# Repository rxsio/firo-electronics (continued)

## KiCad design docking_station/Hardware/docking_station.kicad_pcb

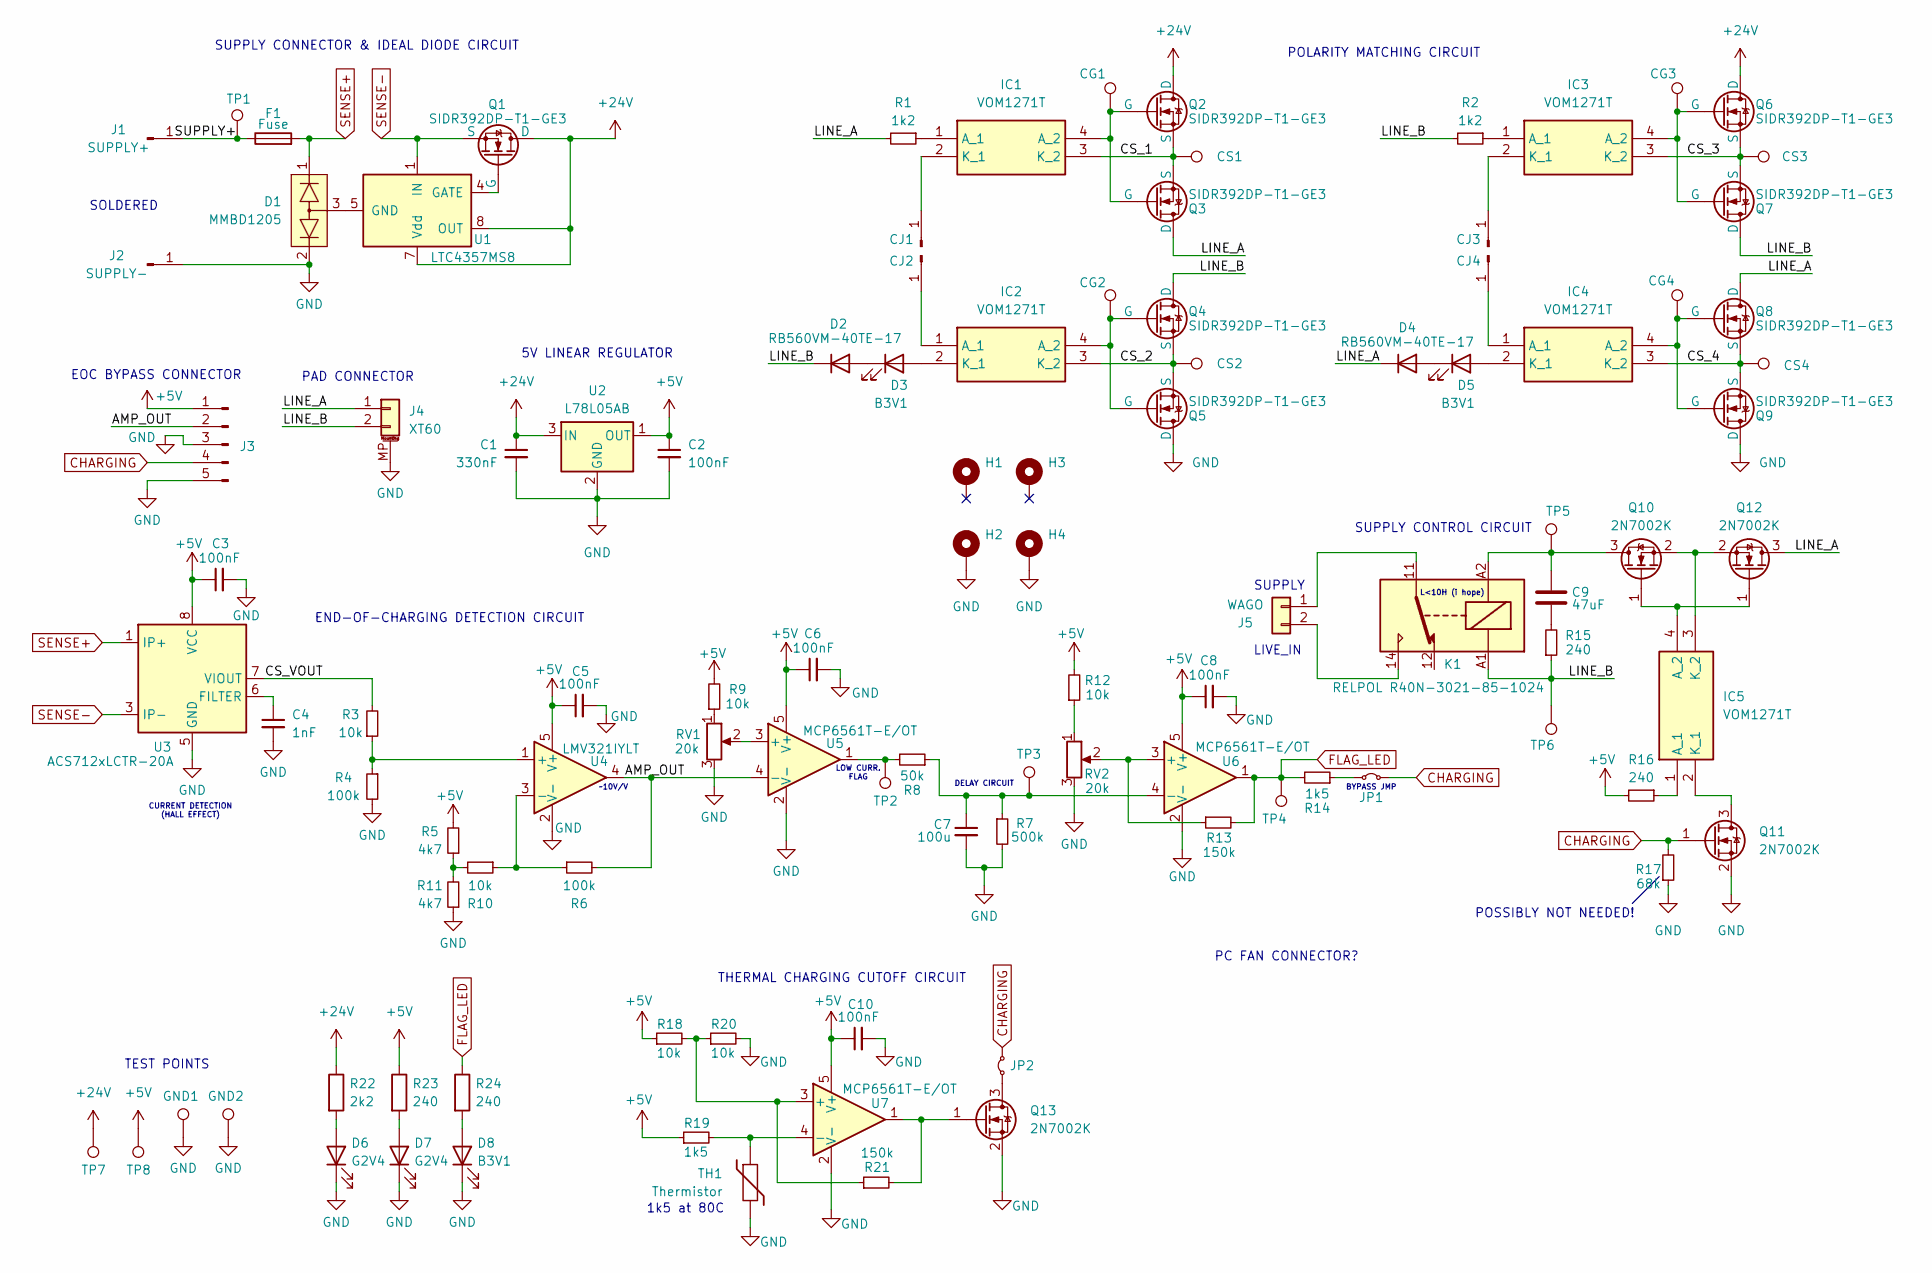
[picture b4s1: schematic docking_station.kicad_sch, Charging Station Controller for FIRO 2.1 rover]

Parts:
C1: 330nF; C_0805_2012Metric
C2, C3, C5, C6, C8, C10: 100nF; C_0805_2012Metric
C4: 1nF; C_0805_2012Metric
C7: 100u; C_1206_3216Metric
C9: 47uF; C_2220_5750Metric
CG1, CG2, CG3, CG4: TestPoint; TestPoint_Pad_D2.0mm
CJ1, CJ2, CJ3, CJ4: 20AWG SMD
CS1, CS2, CS3, CS4: TestPoint; TestPoint_Pad_D2.0mm
D1: MMBD1205; SOT-23
D2, D4: RB560VM-40TE-17; D_SOD-323F
D3, D5, D8: B3V1; LED_0805_2012Metric
D6, D7: G2V4; LED_0805_2012Metric
F1: Fuse; firo_fuse
GND1, GND2: TestPoint; TestPoint_Bridge_Pitch3.81mm_Drill1.3mm
H1, H2, H3, H4: MountingHole_Pad; MountingHole_3.2mm_M3_Pad_Via
IC1, IC2, IC3, IC4, IC5: VOM1271T; SOP254P675X240-4N; Manufacturer_Part_Number VOM1271T
J1: SUPPLY+; 14 AWG THT
J2: SUPPLY-; 14 AWG THT
J3: Conn_01x05_Pin; PinHeader_1x05_P2.54mm_Vertical
J4: XT60; AMASS_XT60PW-F-MP
J5: WAGO; WAGO 2601-3102
JP1, JP2: Jumper_2_Small_Bridged; SolderJumper-2_P1.3mm_Bridged2Bar_RoundedPad1.0x1.5mm
K1: RELPOL R40N-3021-85-1024; Relpol R40N
Q1, Q2, Q3, Q4, Q5, Q6, Q7, Q8, Q9: SIDR392DP-T1-GE3; PowerPAK_SO-8DC for VISHAY SIDR392DP-T1-GE3
Q10, Q11, Q12, Q13: 2N7002K; SOT-23
R1, R2: 1k2; R_1206_3216Metric
R3, R9, R10, R12, R18, R20: 10k; R_0402_1005Metric
R4, R6: 100k; R_0402_1005Metric
R5, R11: 4k7; R_0402_1005Metric
R7: 500k; R_0402_1005Metric
R8: 50k; R_0402_1005Metric
R13, R21: 150k; R_0402_1005Metric
R14, R19: 1k5; R_0402_1005Metric
R15, R16, R23, R24: 240; R_0805_2012Metric
R17: 68k; R_0402_1005Metric
R22: 2k2; R_1206_3216Metric
RV1, RV2: 20k; BOURNS_3313J-1_SMD
TH1: Thermistor; R_Axial_DIN0204_L3.6mm_D1.6mm_P2.54mm_Vertical
TP1, TP2, TP3, TP4, TP5, TP6, TP7, TP8: TestPoint; TestPoint_Pad_D2.0mm
U1: LTC4357MS8; MSOP-8_3x3mm_P0.65mm
U2: L78L05AB; SOT-89-3
U3: ACS712xLCTR-20A; SOIC-8_3.9x4.9mm_P1.27mm
U4: LMV321IYLT; SOT-23-5
U5, U6, U7: MCP6561T-E/OT; SOT-23-5

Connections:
+5V: C2.1, C3.1, C5.1, C6.1, C8.1, C10.1, J3.1, R5.2, R9.2, R12.2, R16.2, R18.1, R19.1, R23.1, TP8.1, U2.1 (OUT), U3.8 (VCC), U4.5 (V+), U5.5 (V+), U6.5 (V+), U7.5 (V+)
+24V: C1.1, Q1.3 (D), Q2.3 (D), Q6.3 (D), R22.1, TP7.1, U1.7 (Vdd), U1.8 (OUT), U2.3 (IN)
/AMP_OUT: J3.2, R6.2, U4.4, U5.4 (-)
/CS_1: CS1.1, IC1.3 (K_2), Q2.1 (S), Q3.1 (S)
/CS_2: CS2.1, IC2.3 (K_2), Q4.1 (S), Q5.1 (S)
/CS_3: CS3.1, IC3.3 (K_2), Q6.1 (S), Q7.1 (S)
/CS_4: CS4.1, IC4.3 (K_2), Q8.1 (S), Q9.1 (S)
/CS_VOUT: R3.2, U3.7 (VIOUT)
/LINE_A: D4.1 (K), J4.1, Q3.3 (D), Q8.3 (D), Q12.3 (D), R1.2
/LINE_B: D2.1 (K), J4.2, K1.A1, Q4.3 (D), Q7.3 (D), R2.2, R15.1, TP6.1
/SUPPLY+: F1.1, J1.1, TP1.1
CHARGING: J3.4, JP1.2 (B), JP2.2 (B), Q11.1 (G), R17.2
FLAG_LED: R13.2, R14.2, R24.1, TP4.1, U6.1
GND: C1.2, C2.2, C3.2, C4.2, C5.2, C6.2, C7.2, C8.2, C10.2, D1.2, D6.1 (K), D7.1 (K), D8.1 (K), GND1.1, GND2.1, H2.1, H4.1, J2.1, J3.3, J3.5, J4.MP (MountPin), Q5.3 (D), Q9.3 (D), Q11.2 (S), Q13.2 (S), R4.2, R7.2, R11.1, R17.1, R20.2, RV1.3, RV2.3, TH1.2, U2.2 (GND), U3.5 (GND), U4.2 (V-), U5.2 (V-), U6.2 (V-), U7.2 (V-)
unnamed: C9.2, R15.2
unnamed: CJ1.1, IC1.2 (K_1)
unnamed: CJ2.1, IC2.1 (A_1)
unnamed: CJ3.1, IC3.2 (K_1)
unnamed: CJ4.1, IC4.1 (A_1)
unnamed: D2.2 (A), D3.1 (K)
unnamed: D3.2 (A), IC2.2 (K_1)
unnamed: D4.2 (A), D5.1 (K)
unnamed: D5.2 (A), IC4.2 (K_1)
unnamed: D6.2 (A), R22.2
unnamed: D7.2 (A), R23.2
unnamed: D8.2 (A), R24.2
unnamed: IC1.1 (A_1), R1.1
unnamed: CG1.1, IC1.4 (A_2), Q2.2 (G), Q3.2 (G)
unnamed: CG2.1, IC2.4 (A_2), Q4.2 (G), Q5.2 (G)
unnamed: IC3.1 (A_1), R2.1
unnamed: CG3.1, IC3.4 (A_2), Q6.2 (G), Q7.2 (G)
unnamed: CG4.1, IC4.4 (A_2), Q8.2 (G), Q9.2 (G)
unnamed: IC5.1 (A_1), R16.1
unnamed: IC5.4 (A_2), Q10.1 (G), Q12.1 (G)
unnamed: IC5.2 (K_1), Q11.3 (D)
unnamed: IC5.3 (K_2), Q10.2 (S), Q12.2 (S)
unnamed: J5.1, K1.11
unnamed: J5.2, K1.14
unnamed: JP1.1 (A), R14.1
unnamed: JP2.1 (A), Q13.3 (D)
unnamed: Q1.2 (G), U1.4 (GATE)
unnamed: C9.1, K1.A2, Q10.3 (D), TP5.1
unnamed: Q13.1 (G), R21.2, U7.1
unnamed: R8.2, TP2.1, U5.1
unnamed: R9.1, RV1.1
unnamed: R5.1, R10.2, R11.2
unnamed: R12.1, RV2.1
unnamed: D1.3, U1.5 (GND)
unnamed: C4.1, U3.6 (FILTER)
unnamed: R3.1, R4.1, U4.1 (+)
unnamed: R6.1, R10.1, U4.3 (-)
unnamed: RV1.2, U5.3 (+)
unnamed: R13.1, RV2.2, U6.3 (+)
unnamed: C7.1, R7.1, R8.1, TP3.1, U6.4 (-)
unnamed: R18.2, R20.1, R21.1, U7.3 (+)
unnamed: R19.2, TH1.1, U7.4 (-)
SENSE+: D1.1, F1.2, U3.1 (IP+), U3.2 (IP+)
SENSE-: Q1.1 (S), U1.1 (IN), U3.3 (IP-), U3.4 (IP-)

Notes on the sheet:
EOC BYPASS CONNECTOR
PC FAN CONNECTOR?
END-OF-CHARGING DETECTION CIRCUIT
~10V/V
SOLDERED
SUPPLY CONNECTOR & IDEAL DIODE CIRCUIT
5V LINEAR REGULATOR
1k5 at 80C
SUPPLY CONTROL CIRCUIT
CURRENT DETECTION (HALL EFFECT)
LIVE_IN
LOW CURR. FLAG
POSSIBLY NOT NEEDED!
DELAY CIRCUIT
PAD CONNECTOR
POLARITY MATCHING CIRCUIT
BYPASS JMP
TEST POINTS
SUPPLY
THERMAL CHARGING CUTOFF CIRCUIT
L<10H (i hope)

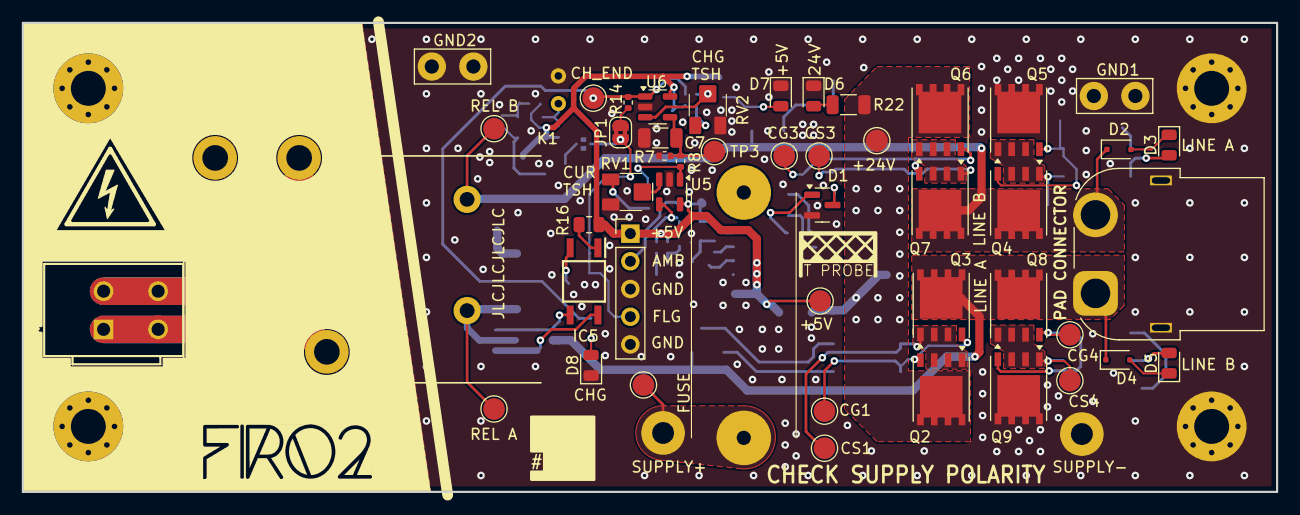
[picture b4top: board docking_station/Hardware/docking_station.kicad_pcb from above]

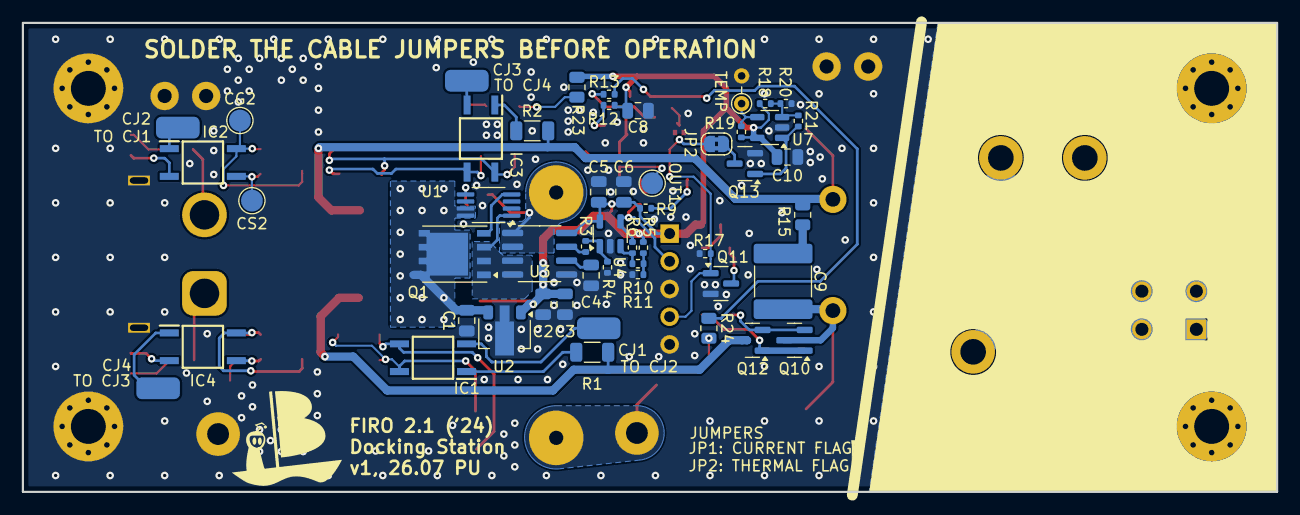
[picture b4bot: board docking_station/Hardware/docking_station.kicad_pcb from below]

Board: 2 copper layers, 115.0 x 43.0 mm, 105 parts (51 on the bottom side), 58 nets.

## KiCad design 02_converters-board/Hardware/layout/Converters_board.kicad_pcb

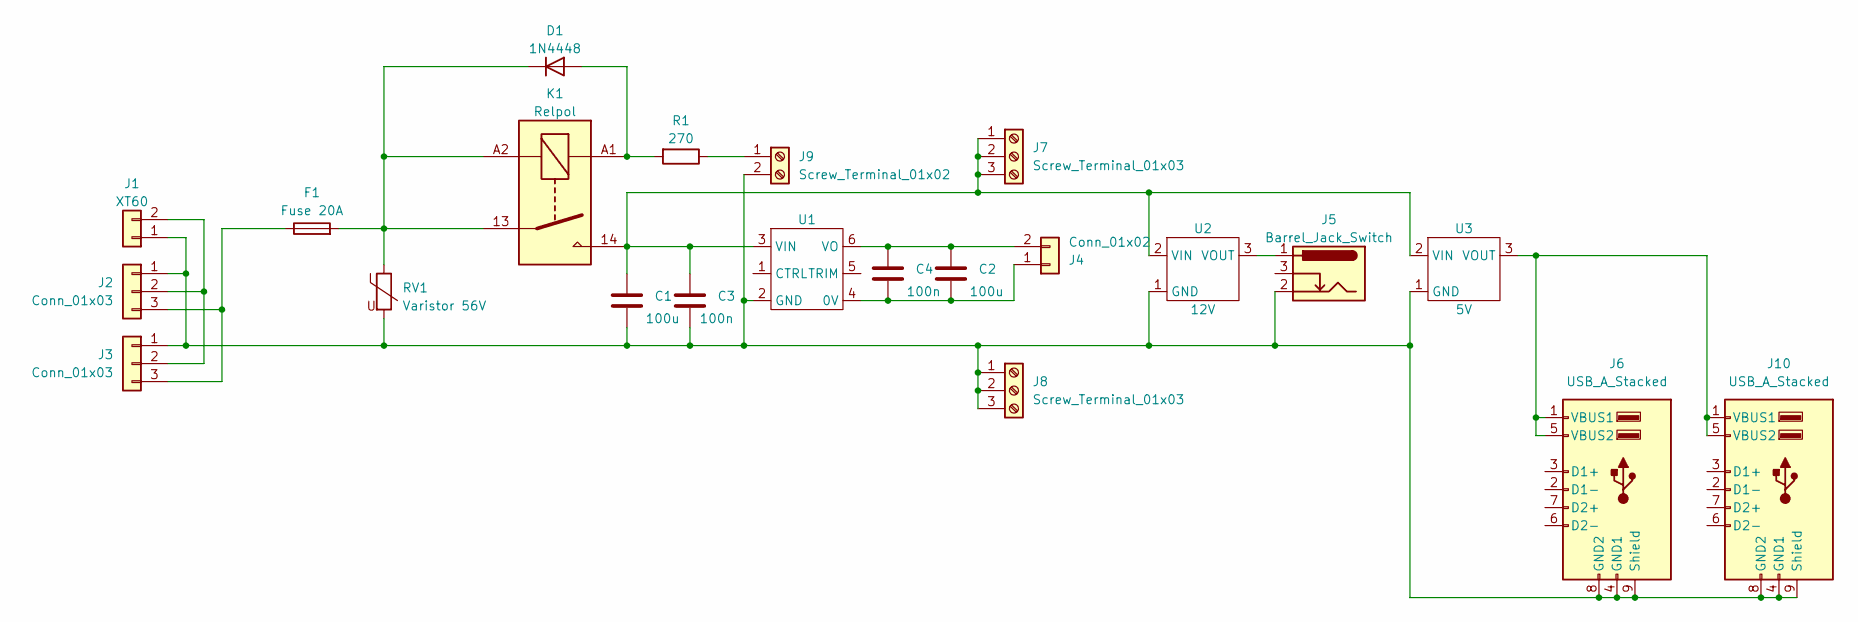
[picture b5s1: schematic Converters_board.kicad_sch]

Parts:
C1, C2: 100u; C_Radial_D10.0mm_H12.5mm_P5.00mm
C3, C4: 100n; C_Disc_D3.0mm_W1.6mm_P2.50mm
D1: 1N4448; D_DO-35_SOD27_P7.62mm_Horizontal
F1: Fuse 20A; Fuseholder_Littelfuse_100_series_5x20mm
J1: XT60; AMASS_XT60-M_1x02_P7.20mm_Vertical
J2, J3: Conn_01x03; AMASS_MR60-F_1x02_P7.20mm_Vertical
J4: Conn_01x02; Phoenix
J5: Barrel_Jack_Switch; BarrelJack_Horizontal
J6, J10: USB_A_Stacked; USB_A_Wuerth_61400826021_Horizontal_Stacked
J7, J8: Screw_Terminal_01x03; Wago_01x03_3,5mm
J9: Screw_Terminal_01x02; Wago_01x02_3,5mm
K1: Relpol; Relay_SPST_RAYEX-L90AS
R1: 270; R_Axial_DIN0309_L9.0mm_D3.2mm_P12.70mm_Horizontal
RV1: Varistor 56V; RV_Disc_D15.5mm_W3.9mm_P7.5mm
U1: Converter_PDQE15-D
U2: 12V; Converter_12V
U3: 5V; Converter_5V

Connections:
unnamed: D1.2 (A), K1.A1, R1.2
unnamed: D1.1 (K), F1.2, K1.13, K1.A2, RV1.1
unnamed: C1.2, C3.2, J1.1, J2.1, J3.1, J5.2, J6.4 (GND1), J6.8 (GND2), J6.9 (Shield), J8.1, J8.2, J8.3, J9.2, J10.4 (GND1), J10.8 (GND2), J10.9 (Shield), RV1.2, U1.2 (GND), U2.1 (GND), U3.1 (GND)
unnamed: J1.2, J2.2, J3.2
unnamed: F1.1, J2.3, J3.3
unnamed: C2.2, C4.2, J4.1, U1.4 (0V)
unnamed: C2.1, C4.1, J4.2, U1.6 (VO)
unnamed: C1.1, C3.1, J7.1, J7.2, J7.3, K1.14, U1.3 (VIN), U2.2 (VIN), U3.2 (VIN)
unnamed: J9.1, R1.1
unnamed: J6.1 (VBUS1), J6.5 (VBUS2), J10.1 (VBUS1), J10.5 (VBUS2), U3.3 (VOUT)
unnamed: J5.1, U2.3 (VOUT)

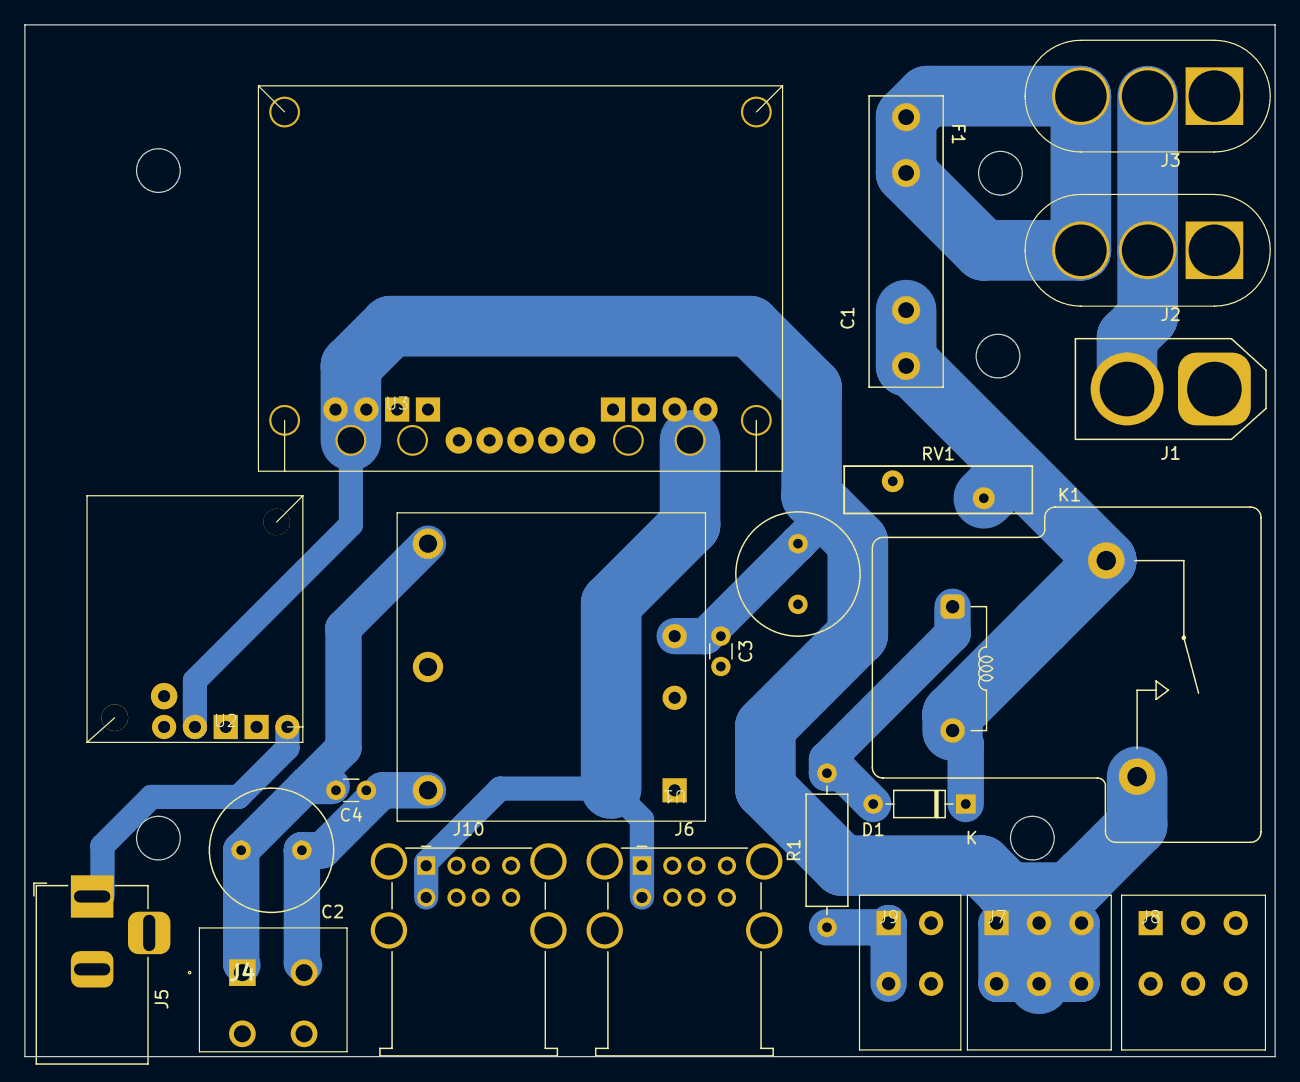
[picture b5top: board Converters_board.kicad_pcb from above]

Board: 2 copper layers, 103.0 x 85.0 mm, 22 parts (0 on the bottom side), 11 nets.

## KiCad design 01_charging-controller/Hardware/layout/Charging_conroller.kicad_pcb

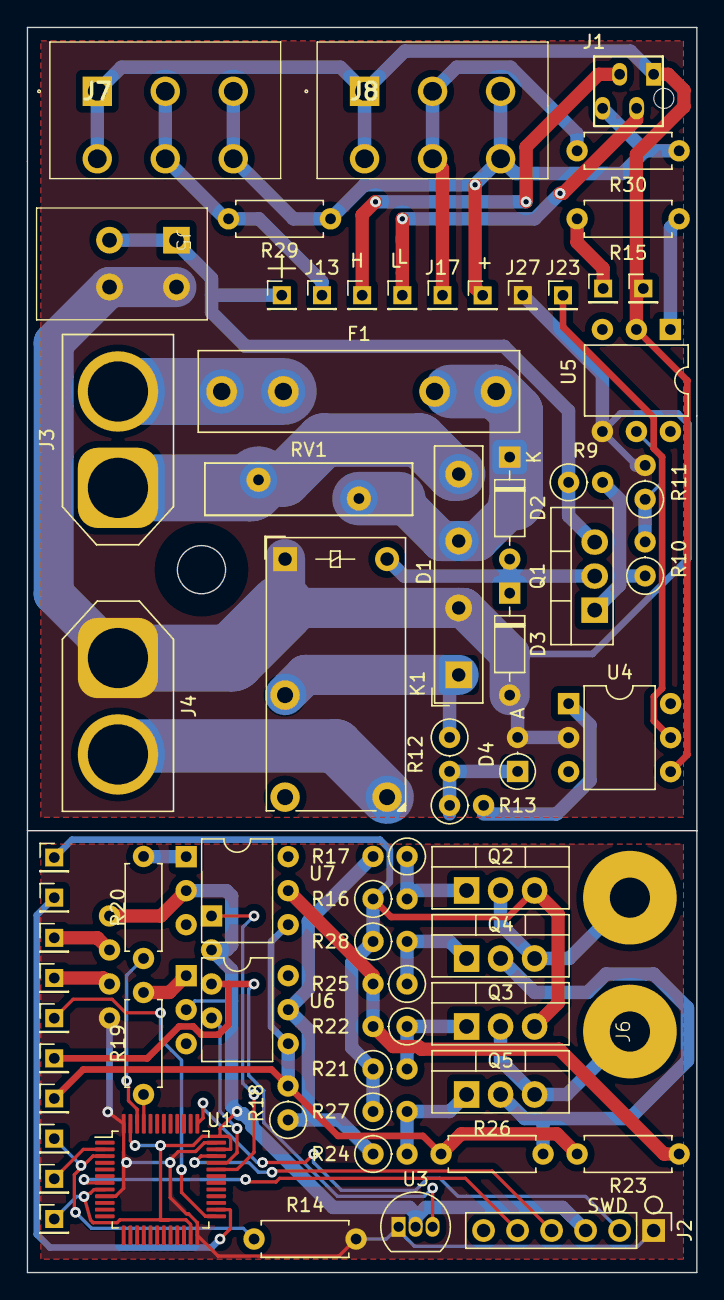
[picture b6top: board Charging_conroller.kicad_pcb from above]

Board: 2 copper layers, 50.0 x 93.0 mm, 69 parts (1 on the bottom side), 48 nets.

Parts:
D1: D_Bridge_+-AA; Diode_Bridge_19.0x3.5x10.0mm_P5.0mm
D2, D3: BAV21; D_DO-35_SOD27_P7.62mm_Horizontal
D4: BZX79C; D_DO-35_SOD27_P2.54mm_Vertical_AnodeUp
F1: Fuse; Fuseholder_Littelfuse_100_series_5x20mm
J1: CAN; CONN-TE-MICROMATCH-2X2-PTH-BOSS
J2: SWD; PinHeader_1x06_P2.54mm_Vertical
J3: LAD; AMASS_XT60-M_1x02_P7.20mm_Vertical
J4: BAT; AMASS_XT60-F_1x02_P7.20mm_Vertical
J5: ZAS; Wago_01x02_3,5mm
J6: MOTOR; Motor
J7, J8: Conn_01x03; Phoenix_ICV_3_vertical
J9, J10, J11, J12, J13, J14, J15, J16, J17, J18, J19, J20, J21, J22, J23, J24, J25, J26, J27, J28: Conn_01x01; PinHeader_1x01_P2.00mm_Vertical
K1: FINDER-32.21-x000; Relay_SPDT_Finder_32.21-x000
Q1, Q2, Q3, Q4, Q5: BD680; TO-220-3_Vertical
R9, R10, R11, R12, R13, R16, R17, R18, R21, R22, R24, R25, R27, R28: R; R_Axial_DIN0207_L6.3mm_D2.5mm_P2.54mm_Vertical
R14, R15, R19, R20, R23, R26, R29, R30: R; R_Axial_DIN0207_L6.3mm_D2.5mm_P7.62mm_Horizontal
RV1: Varistor; RV_Disc_D15.5mm_W3.9mm_P7.5mm
U1: STM32F103CBTx; LQFP-48_7x7mm_P0.5mm
U2: MCP2562-E-P; DIP-8_W7.62mm
U3: L78L33_TO92; TO-92_Inline
U4, U5, U6, U7: 4N25; DIP-6_W7.62mm

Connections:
+3.3V: J2.1, R14.1, U1.9 (VDDA), U1.24 (VDD), U1.36 (VDD), U1.48 (VDD), U2.5 (Vio), U3.1 (VO)
GND: J1.1, J2.3, J7.1, J8.1, J19.1, J20.1, U1.8 (VSSA), U1.23 (VSS), U1.35 (VSS), U1.47 (VSS), U2.2 (VSS), U2.8 (STBY), U3.2 (GND), U4.4, U5.2, U6.2, U7.2
GNDPWR: D1.2 (-), D3.2 (A), D4.2 (A), J4.1, J5.2, J27.1, J28.1, K1.A1, R11.2, R18.2, R23.2, R26.2, U4.2, U5.4, U6.4, U7.4
M_L: R19.2, U1.45 (PB8)
M_R: R20.2, U1.46 (PB9)
unnamed: D1.1 (+), K1.11, R12.1
unnamed: D2.2 (A), D3.1 (K), K1.A2, Q1.2 (C)
unnamed: D1.3, D2.1 (K), F1.2, RV1.1
unnamed: D4.1 (K), R12.2, R13.1
unnamed: J1.2, J15.1
unnamed: J1.3, J12.1
unnamed: J1.4, J7.3, J8.3, J25.1, R29.1, R30.1
unnamed: J2.2, U1.37 (PA14)
unnamed: J2.4, U1.34 (PA13)
unnamed: J2.5, U1.7 (NRST)
unnamed: D1.4, J3.1, RV1.2
unnamed: F1.1, J3.2
unnamed: J4.2, K1.12
unnamed: J5.1, J9.1, Q1.3 (E), R9.1
unnamed: J6.1, Q3.2 (C), Q5.3 (E)
unnamed: J6.2, Q2.2 (C), Q4.3 (E)
unnamed: J10.1, Q2.3 (E), Q3.3 (E), R16.1, R21.1, R27.1, R28.1
unnamed: J11.1, U2.7 (CANH)
unnamed: J7.2, J13.1, R29.2
unnamed: J14.1, U1.26 (PB13)
unnamed: J16.1, U2.6 (CANL)
unnamed: J8.2, J17.1, R30.2
unnamed: J18.1, U1.25 (PB12)
unnamed: J21.1, R15.2
unnamed: J23.1, U4.5
unnamed: J26.1, U2.3 (VDD), U3.3 (VI)
unnamed: Q1.1 (B), R9.2, R10.1
unnamed: Q2.1 (B), R16.2, R17.1
unnamed: Q3.1 (B), R21.2, R22.1
unnamed: Q4.1 (B), R25.1, R28.2
unnamed: Q4.2 (C), Q5.2 (C), R26.1
unnamed: Q5.1 (B), R24.2, R27.2
unnamed: R10.2, R11.1, U5.5
unnamed: R13.2, U4.1
unnamed: R15.1, U5.1
unnamed: R17.2, R18.1, R24.1, U6.5
unnamed: R19.1, U6.1
unnamed: R20.1, U7.1
unnamed: R22.2, R23.1, R25.2, U7.5
unnamed: U1.32 (PA11), U2.1 (TXD)
unnamed: U1.33 (PA12), U2.4 (RXD)
PULSE: J22.1, U1.2 (PC13)
SENSE: J24.1, R14.2, U1.3 (PC14)

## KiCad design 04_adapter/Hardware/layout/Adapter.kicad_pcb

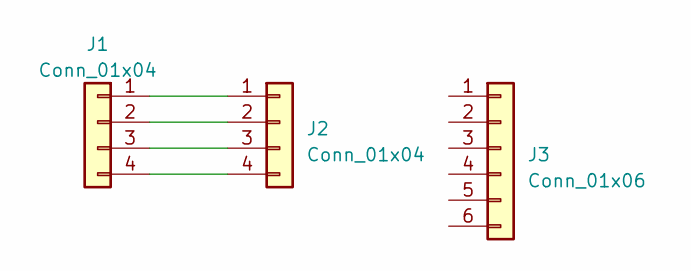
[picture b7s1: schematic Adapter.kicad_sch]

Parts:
J1: Conn_01x04; IDC-Header_2x03_P2.54mm_Vertical
J2: Conn_01x04; FanPinHeader_1x04_P2.54mm_Vertical
J3: Conn_01x06; PinHeader_1x06_P2.54mm_Vertical

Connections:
unnamed: J1.1, J2.1
unnamed: J1.2, J2.2
unnamed: J1.3, J2.3
unnamed: J1.4, J2.4

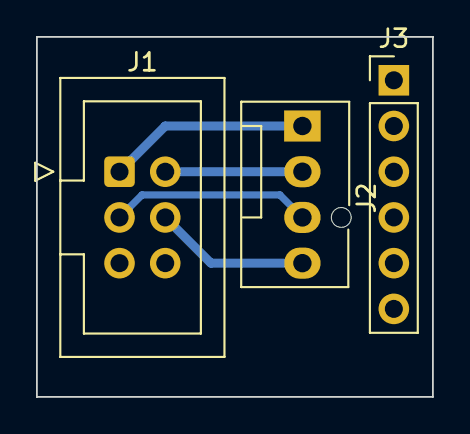
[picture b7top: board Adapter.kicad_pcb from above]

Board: 2 copper layers, 22.0 x 20.0 mm, 3 parts (0 on the bottom side), 4 nets.

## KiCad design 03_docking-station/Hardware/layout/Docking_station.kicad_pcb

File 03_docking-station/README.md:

# Docking Station
## Overview

This project focuses on the electronics system for the FIRO rover's docking station. The docking station is a flat module similar to a floor cable cover, featuring two exposed copper plates. When the rover docks, it deploys two copper probes to establish an electrical connection with these plates. The rover can dock from either side of the station. 

This design addresses uncertainties regarding the docking station's placement inside the FLASH accelerator. It can be positioned anywhere without creating obstructions or safety hazards. However, due to its easy accessibility and exposed copper plates, the docking station must only be powered when used by the rover, to prevent accidental activation by humans. It should also be protected against short circuits caused by metal tools left on the station.

To maintain a flat profile and avoid obstructing the corridor, the electronics system is housed in a separate module that can be placed conveniently on the side of the corridor.

<!--## Usage
Provide instructions for user how to use or interact with the PCB 

### Pinout
Include a pinout schematic. This can help users understand how to interface with the PCB.

### Troubleshooting
Describe common issues that may arise during the PCB usage. Include guidance on identifying and resolving these issues. -->

## Design
### Requirements
- The docking station must be completely powered off when not in use by the rover.
  - It should power off automatically after the rover stops charging.
  - Activation cannot be triggered accidentally by humans:
    - The rover must initially power the station to start charging.
- The docking station should support charging from both sides.
  - It should adjust the polarization of the copper pads based on the rover's initialization pulse.
- The docking station must cut off power in case of a short circuit between the copper pads.

<!-- ### Components
This section should highlight the most important components and their functions. 

### Schematic
Include an exported image of the PCB schematic.  
Optionally describe any relevant details about the schematic design

### Layout
Include exported images of the PCB layouts  
- Combined layout with dimensions. Include all important dimensions: PCB width and height, mounting holes size and position, etc.  
- Combined layout without dimensions  
- Separate layouts for each layer  
Optionally describe any relevant details about the layout

### Reference Documentation
Include links to relevant reference documents such as datasheets for the components. When possible, host the documents in the project repository. It will guarantee they are easily accessible in the future, even If the original links would be no longer valid.

## Firmware
### Overview
Briefly describe function of the firmware. You may also describe firmware architecture, key components and dependencies.

### Usage
Describe how to use the firmware. Include information about:

- user interfaces or commands available  
- settings, or parameters that can be customized

### Development  
- Installing dependencies required for the development  
- Setting up development environment  
- Uploading firmware to the target device

## Manufacturing
### Manufacturing Considerations
Include any manufacturing considerations for the PCB design, such as panelization, solder mask requirements, or impedance control.

### Assembly Instructions
Include any specific guidelines or precautions that need to be followed during the assembly process.

### Testing
Describe the testing procedures and methodologies used to verify the functionality of the PCB. 

## Conclusions
Summarize the key findings of the PCB project. Provide recommendations for future improvements. -->

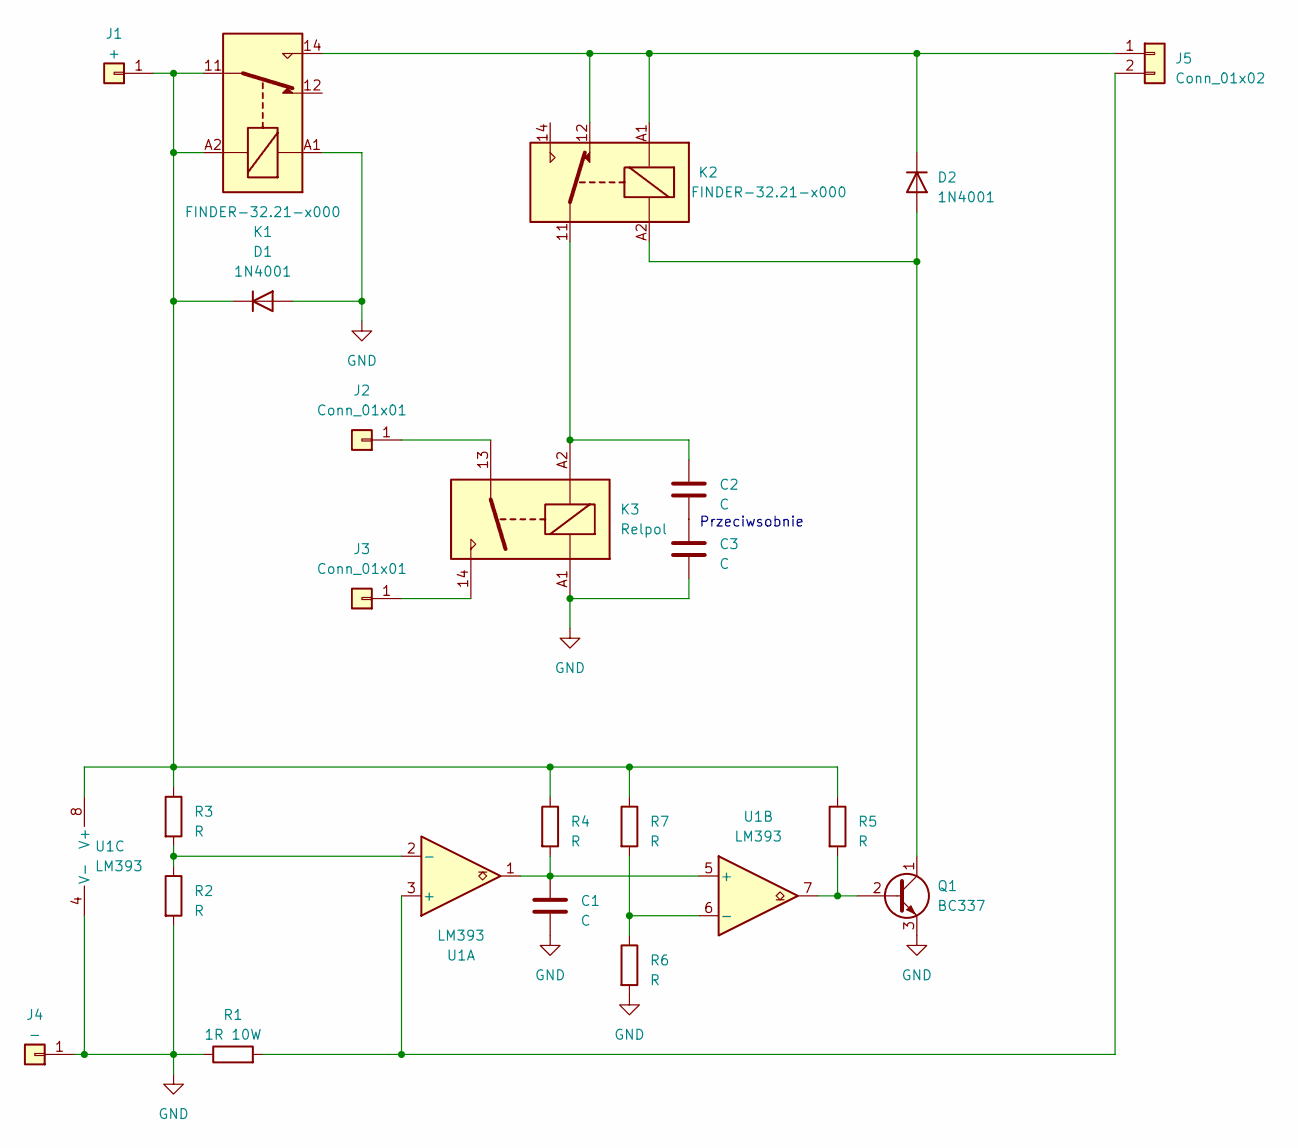
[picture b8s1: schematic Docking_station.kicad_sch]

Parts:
C1: C; Phoenix
C2, C3: C; C_Radial_D8.0mm_H11.5mm_P3.50mm
D1, D2: 1N4001; D_DO-41_SOD81_P10.16mm_Horizontal
J1: +; SolderWire-1.5sqmm_1x01_D1.7mm_OD3.9mm
J2, J3: Conn_01x01; SolderWire-1.5sqmm_1x01_D1.7mm_OD3.9mm
J4: -; SolderWire-1.5sqmm_1x01_D1.7mm_OD3.9mm
J5: Conn_01x02; Phoenix
K1, K2: FINDER-32.21-x000; Relay_SPDT_Finder_36.11
K3: Relpol; Relay_SPST_RAYEX-L90AS
Q1: BC337; TO-92L_Inline_Wide
R1: 1R 10W; R_Axial_Power_L50.0mm_W9.0mm_P60.96mm
R2, R3, R4, R5, R6, R7: R; R_Axial_DIN0207_L6.3mm_D2.5mm_P7.62mm_Horizontal
U1: LM393; DIP-8_W7.62mm_Socket

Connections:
GND: C1.2, C3.2, D1.2 (A), J4.1, K1.A1, K3.A1, Q1.3 (E), R1.1, R2.2, R6.2, U1.4 (V-)
unnamed: C2.1, K2.11, K3.A2
unnamed: C2.2, C3.1
unnamed: D1.1 (K), J1.1, K1.11, K1.A2, R3.1, R4.1, R5.1, R7.1, U1.8 (V+)
unnamed: D2.2 (A), K2.A2, Q1.1 (C)
unnamed: D2.1 (K), J5.1, K1.14, K2.12, K2.A1
unnamed: J2.1, K3.13
unnamed: J3.1, K3.14
unnamed: J5.2, R1.2, U1.3 (+)
unnamed: Q1.2 (B), R5.2, U1.7
unnamed: R2.1, R3.2, U1.2 (-)
unnamed: C1.1, R4.2, U1.1, U1.5 (+)
unnamed: R6.1, R7.2, U1.6 (-)

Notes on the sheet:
Przeciwsobnie

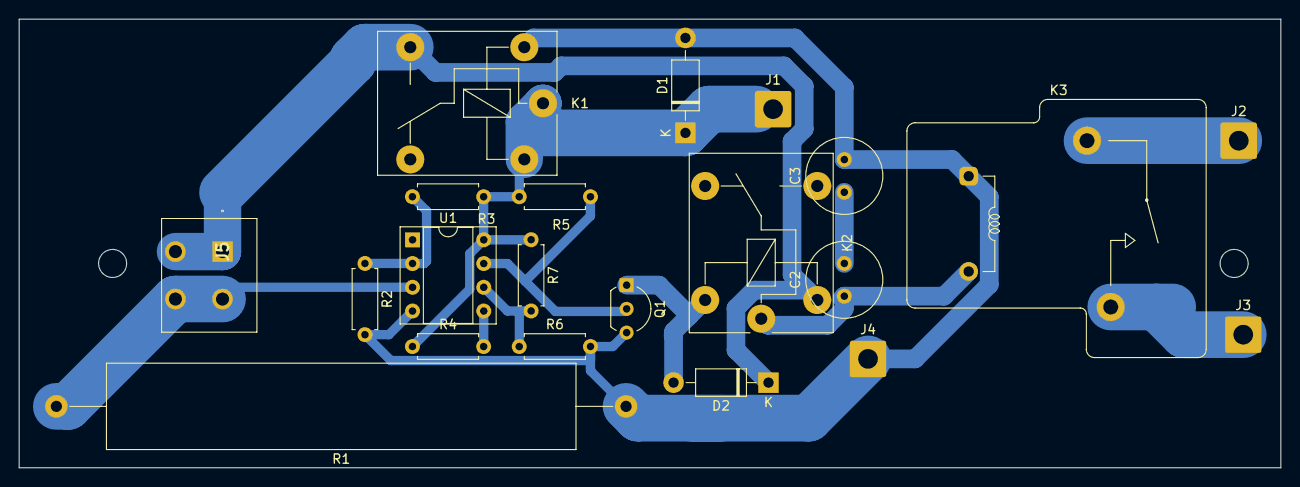
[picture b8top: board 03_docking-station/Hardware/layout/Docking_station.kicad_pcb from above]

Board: 2 copper layers, 135.0 x 48.0 mm, 21 parts (0 on the bottom side), 13 nets.

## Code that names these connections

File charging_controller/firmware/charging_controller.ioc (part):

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Mcu.Name=STM32F103C(8-B)Tx
Mcu.Package=LQFP48
Mcu.UserName=STM32F103CBTx
PA11.Mode=CAN_Activate
PA11.Signal=CAN_RX
PA12.Mode=CAN_Activate
PA12.Signal=CAN_TX
PA13.Mode=Serial_Wire
PA13.Signal=SYS_JTMS-SWDIO
PA14.Mode=Serial_Wire
PA14.Signal=SYS_JTCK-SWCLK
PA3.GPIOParameters=GPIO_Label
PA3.GPIO_Label=MOTOR_RETRACT
PA3.Signal=GPIO_Output
PA4.GPIOParameters=GPIO_Label
PA4.GPIO_Label=MOTOR_DEPLOY
PA4.Signal=GPIO_Output
PA5.GPIOParameters=GPIO_Label
PA5.GPIO_Label=CHARGE_PULSE
PA5.Signal=GPIO_Output
PB10.GPIOParameters=GPIO_Label
PB10.GPIO_Label=BATTERY_CUTOFF
PB10.Signal=GPIO_Output
PB12.GPIOParameters=GPIO_Label
PB12.GPIO_Label=CHARGE_SENSE
PB12.Signal=GPIO_Input
PB13.GPIOParameters=GPIO_Label,GPIO_ModeDefaultEXTI
PB13.GPIO_Label=PROBE_RETRACTED
PB13.GPIO_ModeDefaultEXTI=GPIO_MODE_IT_FALLING
PB13.Signal=GPXTI13
PB14.GPIOParameters=GPIO_Label
PB14.GPIO_Label=PROBE_EXTENDED
PB14.Signal=GPXTI14
PB7.GPIOParameters=GPIO_Label
PB7.GPIO_Label=MOTOR_PWM
PB7.Signal=S_TIM4_CH2
board=custom

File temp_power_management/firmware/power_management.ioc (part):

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Mcu.Name=STM32F103C(8-B)Tx
Mcu.Package=LQFP48
Mcu.UserName=STM32F103CBTx
PA11.Mode=CAN_Activate
PA11.Signal=CAN_RX
PA12.Mode=CAN_Activate
PA12.Signal=CAN_TX
PA13.Mode=Serial_Wire
PA13.Signal=SYS_JTMS-SWDIO
PA14.Mode=Serial_Wire
PA14.Signal=SYS_JTCK-SWCLK
PB0.GPIOParameters=GPIO_Label
PB0.GPIO_Label=BATTERY_VOLTAGE
PB0.Signal=ADCx_IN8
PB6.GPIOParameters=PinState,GPIO_Label
PB6.GPIO_Label=PC_ENABLE
PB6.PinState=GPIO_PIN_SET
PB6.Signal=GPIO_Output
board=custom

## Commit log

2024-07-02 Init
    First port of the electronics content. Filenames have been changed so expect dependency issues (especially in 3d model)
2024-07-03 dependency buxfixes in charging_controller
2024-07-03 minor mistakes fixed; reflected hardware updates
2024-07-04 big changes - deciding between Si or click-clack
2024-07-05 docs: docking station overview and requirements
2024-07-05 docking_station draft finished
    a lot to do still - mostly calculation and review, but the bulk is done and I'm happy
2024-07-07 component_update
2024-07-08 more components chosen
    it's a case of finishing the component choices and exporting the BOM now
2024-07-08 minor update
    some changes to the cutoff circuit
2024-07-09 minor update to current sensing circuit
2024-07-09 major end-of-charging detector update
    That was overwhelming, but will work. I hope. Lots of simulations before me
2024-07-10 almost done
2024-07-11 finished (v1, no flyback yet)
2024-07-11 schematic complete
    snubber parameters set, basic components chosen.
2024-07-11 assigned stock footprints
2024-07-14 added relay footprint
2024-07-14 schematic v1.0. added gitignore
2024-07-14 cleanup & gitignore gaming
2024-07-14 Revert "cleanup & gitignore gaming"
    This reverts commit cecd3991cb5c2ab0070e9d045edcd67cce56664a.
2024-07-14 better cleanup
2024-07-14 more footprints created & assigned
2024-07-14 something
2024-07-15 trochę zmian fpt
2024-07-16 introductory compontent layout
    grouped the components, prepped the group layout. The board does seem doable
2024-07-16 big layout progress
2024-07-16 work still in progress
2024-07-19 almost finished
2024-07-23 MAJOR: PCB re-do begin
    Revert here if needed :P
2024-07-25 big layout updates
2024-07-25 layout complete; footprint review complete
2024-07-26 docking station finished; 3d models & v_design added
2024-07-26 Readability update begin
    Added LEDs
2024-07-27 PCB layout, design and BOM complete; pending review
2024-07-29 File structure & documentation
2024-08-01 we're going deeper; see you on the other side
2024-08-01 preparing for major rework
2024-08-04 i_hate_git_please_end_this
2024-08-05 small changes
2024-08-07 handoff_to_office
2024-08-07 a lot of work done
2024-08-08 gaining_a_level_of_exhaustion_xd
2024-08-09 PCBs possibly finished + some file org
2024-08-10 a lot of work - charging main BOM complete
2024-08-10 last commit before gerber export
2024-08-10 shopping list, gerbers and board updates
2024-08-16 port to office
2024-08-16 work on power management
2024-08-20 minor work, updates to shopping list
2024-08-20 minor work done
2024-08-21 temp_PMS - much done, kill me
2024-08-22 power management progress
2024-08-23 temp_pms bloody FINISHED and ordered.
2024-09-02 feat: gitignore for KiCad v8
2024-09-02 feat: STM32CudeIde gitignore
2024-09-02 feat: Initial charging controller firmware in CubeIde project
2024-09-02 docs: add more comments explaining code and important notes
2024-09-02 docs: Add readme with overview of CAN messages and potential improvements
2024-09-22 feat!: Update pinout to new board and regenerate code with updated CubeIDE
2024-09-24 feat(charging_controller, firmware): Update code logic for new pcb
2024-10-10 docs: update message description - stop charging cmd and status request
2024-11-08 fix!: fixes manually applied to boards post production
2024-11-08 docs: Radiation Effects handbook
2024-11-08 feat: kicad custom components
2024-11-08 feat!: Docking station v2.0 (2024)
2024-11-08 feat!: Charging controller v2 (2024)
    Compatible with new docking station
2024-11-08 feat!: Power Management System v2 (2024)
2024-11-08 chore: August 24 shopping list
2024-11-08 feat: Firmware for charging controller v2 (2024)
2024-11-08 chore: gitignore for KiCAD v8
2024-11-08 chore: STM32CudeIde gitignore
2024-11-08 chore: remove ignored files (.bak, fp-info-cache)
2024-11-20 feat!(charging_controller): Update firmware for simplified charging controller
2024-11-20 feat(power-management): Initial firmware with battery voltage monitoring
2026-05-21 chore: setup branch for FIRO3
2026-05-22 AUX channel schematic init, WIP
2026-05-22 AUX channel init
2026-05-28 Branching test
